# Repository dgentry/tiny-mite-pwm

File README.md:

TinyMite PWM
=============

A small, cheap, programmable PWM controller suitable for driving
LEDs or motors.  Based on 8 pin ATTiny uControllers.

What good is it?  Features:
* Compact (1" x 1.25")
* Can drive two paralleled MOSFETs
* Can take a kickback suppression (flywheel) diode for driving motors or solenoids.
* Programmable since it's based on an AtTiny microcontroller (ATTiny 25, 45, 85, and probably 13 all work).
* Has space for a couple of programmable status LEDs
* Capable of input from a switch or potentiometer
* Can monitor a thermistor for high temperature protection

Choose your MOSFET(s), and if you're driving a
motor, your kickback diode, and have at it.

I have built it with various MOSFETS and kickback diodes, but a good
combination seems to be an IRF2804 (42 volt, 270 amp) and On Semi MBR30H150
(30 amp, 150 volt dual Schottky in a TO-220 package), where it happily
controls a 25 amp fan motor in my Crown Victoria.  In that
application, it's on the edge of needing heat sinks.

A note on PWM and component choices
-----------------------------------
Here's what I have learned about MOSFETs and kickback diodes.

IRF2804s cost something like $3.00 these days, so maybe there's
something newer, better and cheaper (the IRFZ44N looks good to me at
$1.18 each for 10 from Newark).  The parameters to pay attention to
are:
* I_d (Continuous Drain current)
* V_ds (Drain Source voltage), and
* R_dson (On Resistance) at the manufacturer's rated test voltage.

I choose I_d to be at least twice the (fuse) rating of the motor, but
with LEDs you could probably get away with something just above the
total load current.  The IRFZ44 is only rated at 49 amps (vs. 270 amps
for the IRF2804), but that should be OK (with a heatsink) for my 25
amp fan motor.

V_ds must be well above the maximum transient voltage spike you ever
expect, since MOSFETs can instantly fail if you exceed that voltage,
even for a moment.  In a car (nominally 13.6 volts), Automotive rated
MOSFETS like the IRF2804 or the IRFZ44N should be fine, and they have
Vgs ratings of 42 and 55 volts, respectively.

R_dson primarily determines one source of power (heat) you'll have to
dissipate from your MOSFET.  Automotive MOSFETs (in particular, the
IRF2804) have amazingly low R_dson, so they can have crazily high I_d
ratings (270 amps continuous), limited only by the TO-220 packaging.
Power is I^2 * R, so 25 amps * 2.3 mOhm = 1.5 watts, which technically
requires a heatsink above ~ 50 degrees C ambient, but my car interior
doesn't stay at 50 degrees C when I'm running the A/C + fan.

The other source of heat is switching losses -- every time the PWM
changes from high to low or the other way around, for a very brief
period (and we make it as brief as possible, in the microseconds
range) some current is flowing through the MOSFET with moderate
resistance.  At lower switching frequencies (say 1 khz to 10 khz), the
several microseconds switching time is negligible compared to the
pulse width (1 millisecond to 100 microseconds).  As the frequencies
get higher (say 20 khz to 100khz giving 50 microsecond to 10
microsecond pulses), the switching time is a significant fraction of
the pulse width, so you have to pay attention to the heat generated
then.  I haven't noticed any whine from my motor or circuit (it's in a
noisy car, after all), so switching at 2 khz doesn't add much in the
way of switching losses, while the motor still "sees" relatively
smooth power.

Datasheets
----------
IRF2804:  http://www.irf.com/product-info/datasheets/data/irf2804.pdf
http://www.newark.com/international-rectifier/irf2804pbf/n-ch-mosfet-40v-270a-to-220ab/dp/63J7214

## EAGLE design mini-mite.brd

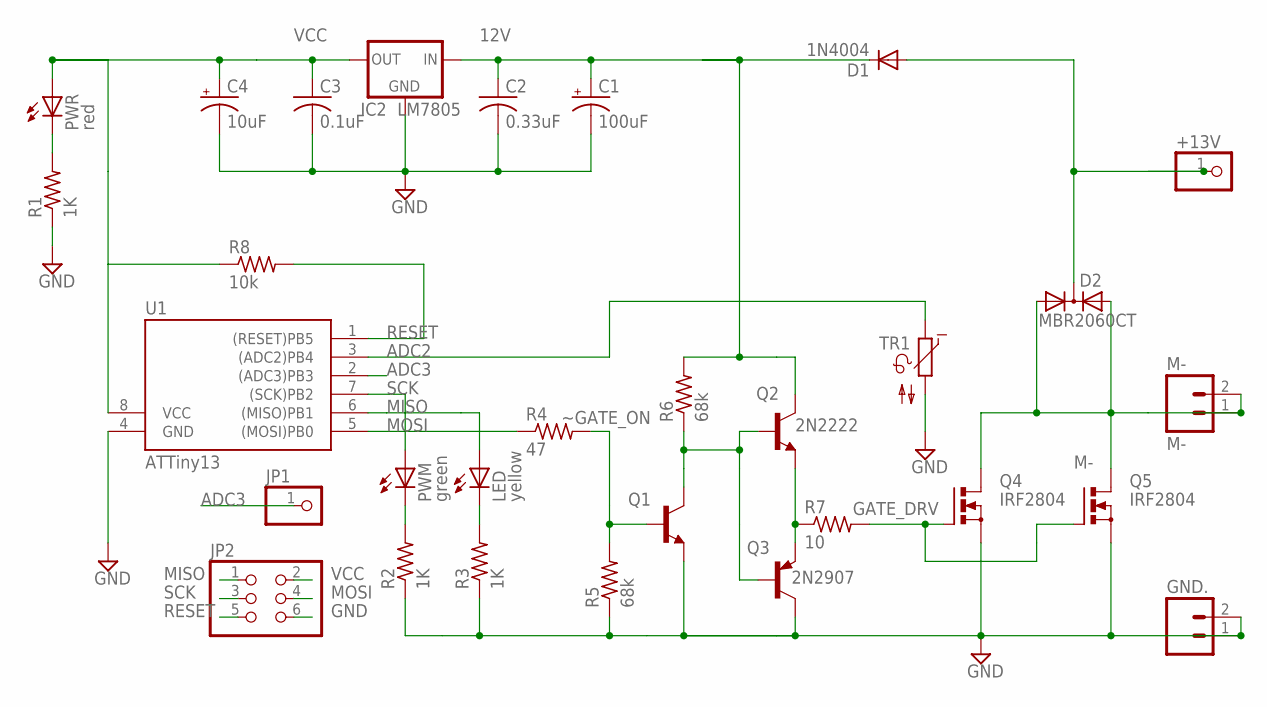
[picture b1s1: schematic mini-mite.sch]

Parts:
+13V: 1X01
C1: 100uF; E2,5-6
C2: 0.33uF; C025-025X050
C3: 0.1uF; C025-025X050
C4: 10uF; E2,5-6
D1: 1N4004; DO41-10
D2: MBR2060CT; TO220ABS
GND.: M02LOCK_LONGPADS; 1X02_LOCK_LONGPADS
IC2: LM7805; 78XXS
JP1: PINHD-1X1; 1X01
JP2: PINHD-2X3; 2X03
LED: yellow; LED5MM
M-: M-; 1X02_LOCK_LONGPADS
PWM: green; LED5MM
PWR: red; LED5MM
Q1, Q2: 2N2222; TO92-EBC-OVAL
Q3: 2N2907; TO92-EBC-OVAL
Q4, Q5: IRF2804; TO220BV
R1, R2, R3: 1K; 0207/7
R4: 47; 0207/10
R5, R6: 68k; 0207/7
R7: 10; 0207/7
R8: 10k; 0207/7
TR1: NTC642-6; P642
U1: ATTiny13; DIL08

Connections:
12V: C1.+, C2.1, D1.C, IC2.IN, Q2.C, R6.2
+13V: +13V.1, D1.A, D2.C
ADC2: TR1.1, U1.3 ((ADC2)PB4)
ADC3: JP1.1, U1.2 ((ADC3)PB3)
GATEON: Q1.C, Q2.B, Q3.B, R6.1
GATE_DRV: Q4.G, Q5.G, R7.2
GND: C1.-, C2.2, C3.2, C4.-, GND..1, GND..2, IC2.GND, JP2.6, Q1.E, Q3.C, Q4.S, Q5.S, R1.1, R2.1, R3.1, R5.1, TR1.2, U1.4 (GND)
M-: D2.A1, D2.A2, M-.1, M-.2, Q4.D, Q5.D
MISO: JP2.1, LED.A, U1.6 ((MISO)PB1)
MOSI: JP2.4, R4.1, U1.5 ((MOSI)PB0)
unnamed: LED.K (C), R3.2
unnamed: Q2.E, Q3.E, R7.1
unnamed: PWR.K (C), R1.2
unnamed: PWM.K (C), R2.2
RESET: JP2.5, R8.2, U1.1 ((RESET)PB5)
SCK: JP2.3, PWM.A, U1.7 ((SCK)PB2)
VCC: C3.1, C4.+, IC2.OUT, JP2.2, PWR.A, R8.1, U1.8 (VCC)
~GATE_ON: Q1.B, R4.2, R5.2

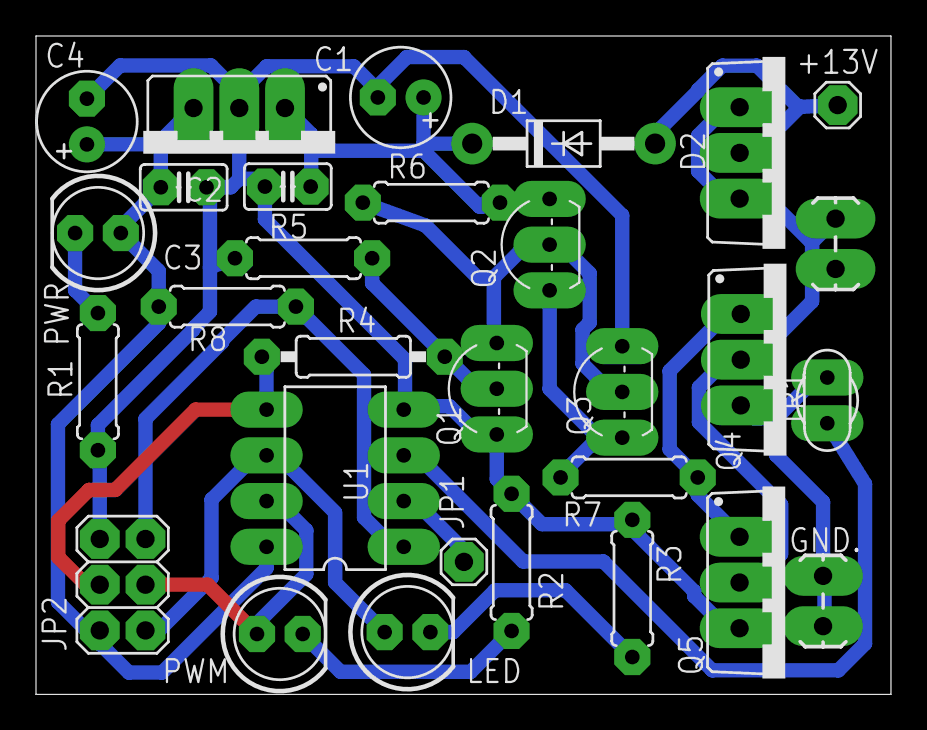
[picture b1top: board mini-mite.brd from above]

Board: 2 copper layers, 47.5 x 36.6 mm, 30 parts (0 on the bottom side), 18 nets.

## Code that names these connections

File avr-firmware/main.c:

/* Name: main.c
 * Author: Dennis Gentry
 * Copyright 2010, Dennis Gentry
 * License: Creative Commons Attribution
 */

/* 
 * Title: PWM for the Neophyte
 * Hardware: ATtiny13
 */
 
//#define F_CPU 9600000UL // Define software reference clock for delay duration
#include <stdlib.h>
#include <avr/io.h>
#include <util/delay.h>
#include <assert.h>


// For hardware PWM, only PB0 or PB1 have timer/counter support
#define PWM_OUT_PIN PB0

#define LED PB2
#define POT PB3  // (aka ADC3)
#define GATE PB1  // The gate of the MOSFETs we want to control
#define TEMP PB4  // (ADC 2) The Thermistor (other leg is grounded)

unsigned char duty_cycle;  // In the 0 - 255 range
#define MIN_DUTY_CYCLE 0
#define MAX_DUTY_CYCLE 255

void mydelay(int ms);
void flash_number(int num);
void flash_number_in_binary(unsigned char num);
unsigned char a_to_d(unsigned char pin);

/* Making variables static for ISRs */

unsigned char temperature;

int main (void)
{
  DDRB |= (1 << LED); // Make LED an output, Will want to blink LED
  DDRB |= (1 << GATE); // Make GATE an output
  DDRB &= ~(1 << TEMP);

  /* Set up to read Pot */
  DDRB &= ~(1<< POT); // Set POT as an input (0-5v)
  ADCSRA |= (1 << ADEN)| // Analog-Digital enable bit
    (1 << ADPS1)| // set prescaler to 8 (clock / 8)
    (1 << ADPS0); // set prescaler to 8 (clock / 8)
 

  /* Set up PWM */
  //DDRB |= (1 << PWM_OUT_PIN); // OC0A on PB0
  // COM0A1 - COM0A0 (Set OC0A on Compare Match, clear OC0A at TOP)
  //TCCR0A |= ((1 << COM0A1) | (1 << COM0A0) 
  //	     | (1 << WGM01) | (1 << WGM00)); // WGM01 - WGM00 (set fast PWM)
  //OCR0A = 0; // initialize Output Compare Register A to 0

  //TCCR0B |= (1 << CS01); // Start timer at Fcpu / 256
 

  flash_number_in_binary(0);
  flash_number_in_binary(TEMP);
  flash_number_in_binary(15);
  flash_number_in_binary(POT);

  while (1) {

    // Sample POT to get desired motor speed
    duty_cycle = a_to_d(POT);

    //----------Show ADCH Byte in Led variable brightness indicator---------
 
    if (duty_cycle > 0) {
      PORTB |= (1 << LED);  // Turn on the LED
      PORTB |= (1 << GATE); // and the MOSFETs
    }
    mydelay(duty_cycle);

    // Sample
    temperature = a_to_d(TEMP); //(100K/4.7K thermistor/resistor
			// ~5v - .2v, ~4.1v = 60C, ~2.5v = 100C)

    if (temperature > ((4.5/5.0)*256)) {
      flash_number_in_binary(temperature/32);
    }

    if (duty_cycle < MAX_DUTY_CYCLE) {
      PORTB &= ~(1 << LED);   // Turn off the LED
      PORTB &= ~(1 << GATE);  // and the MOSFETs
    }
    mydelay(MAX_DUTY_CYCLE - duty_cycle);

  }
  return 0; // not reached
}

unsigned char a_to_d(unsigned char pin) 
{
  unsigned char mux = 0;  //(ADC0/PB5 = 00, ADC1/PB2 = 01, ADC2/PB4 = 10, ADC3/PB3 = 11)

  flash_number_in_binary(pin);
  if (pin == PB2) mux = 1;
  else if (pin == PB4) mux = 2;
  else if (pin == PB3) mux = 3;


  ADMUX |= (1 << ADLAR)| // AD result store in (most significant bit in ADCH)
    (mux & ((1 << MUX1) | (1 << MUX0))); // Choose AD input 

  // ADMUX should be 0b001000mm where mm is the mux value
  assert(ADMUX >= 0b00100000 && ADMUX <= 0b00100011);

  flash_number_in_binary(ADMUX);

  ADCSRA |= (1 << ADEN); // Analog-Digital enable bit
  ADCSRA |= (1 << ADSC); // Discard first conversion

  while (ADCSRA & (1 << ADSC)); // wait until conversion is done
    
  ADCSRA |= (1 << ADSC); // start another conversion
 
  while (ADCSRA & (1 << ADSC)); // wait until conversion is done
 
  ADCSRA &= ~(1<<ADEN); // shut down the ADC

  return ADCH;
}
 
 
/*
 *  Flash LED <num> times, then pause.
 */
void flash_number(int num)
{
  int i;
  for (i = 0; i < 4; i++) {
    _delay_ms(50);
  }

  for (i = 0; i < num; i++) {
    PORTB |= (1 << LED);
    _delay_ms(15);
    PORTB ^= (1 << LED); // Invert led bit and show it
    _delay_ms(45);
  }


  for (i = 0; i < 4; i++) {
    _delay_ms(50);
  }
}



/*
 *  Flash <num> in binary on the LED
 */
void flash_number_in_binary(unsigned char num)
{
  char i, j;  // Really only need 4 bits for each of these -- bit pointers into a byte

  for (i = 0; i < 4; i++) {
    _delay_ms(50);
  }

  // Find first set bit (isn't there a libc function for this?)
  for (i = 7; i >= 0 && !(num & (1 << i)); i--);
  // i either points at the first set bit, or -1

  // Always flash at least bits 3 - 0
  if (i<3) i = 3;


  for (j = i; j >= 0; j--) {
    PORTB |= (1 << LED);  // Flame on
    if (num & (1 << j)) {
      _delay_ms(60);
      PORTB &= ~(1 << LED); // Flame off
    } else {
      _delay_ms(10);
      PORTB &= ~(1 << LED); // Flame off
      _delay_ms(50);
    }

    _delay_ms(40);
  }

  for (i = 0; i < 4; i++) {
    _delay_ms(50);
  }
}




void mydelay(int ms)
{
  int i;

  for (i = 0; i < ms; i++) {
    _delay_us(5);
  }
}

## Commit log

2013-04-15 First
2013-04-15 Populate the repo.
2013-04-16 Fixed drive voltage range bug.
2013-04-16 Add datasheet for IRF2804
2014-03-28 Update README.md
    Better name, include dimensions. Should also add pdf of layout somewhere.

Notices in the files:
mini-mite.brd:
(C) 2013, Spudlab
parts and their libraries:
SparkFun: Licensing: CC v3.0 Share-Alike You are welcome to use this library for commercial purposes.
